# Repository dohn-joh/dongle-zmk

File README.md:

Components for a zmk dongle: a reversible pcb that features mounting holes and wiring for a reset button, and a 3D printed case. The pcb is reversible so that you have the option to mount a reset button to the left or right side of the usb port.

## Files:
- gerbers for a promicro compatible reversible pcb
- 3D models for a case
- ergogen code used to generate the pcb

## Bill of materials:
- 4 M2 screws (5-6mm length)
- 4 M2 heatset inserts (any length <5mm will work)
- Panasonic EVQ-PU[A|C|J|L]02K (side-operated momentary switch)
- microcontroller with promicro footprint
- sockets for the mcu or headers that came with the mcu

## Assembly notes:
- PCB design is intended for the mcu to be mounted face down, such that the RAW pin is in the top left corner. 
- Solder the jumper pads on the same side of the pcb that the mcu is mounted to.

This small project was inspired by https://github.com/spe2/zmk_dongle_hardware.
I used ergogen to generate the pcb and designed the case in fusion360.

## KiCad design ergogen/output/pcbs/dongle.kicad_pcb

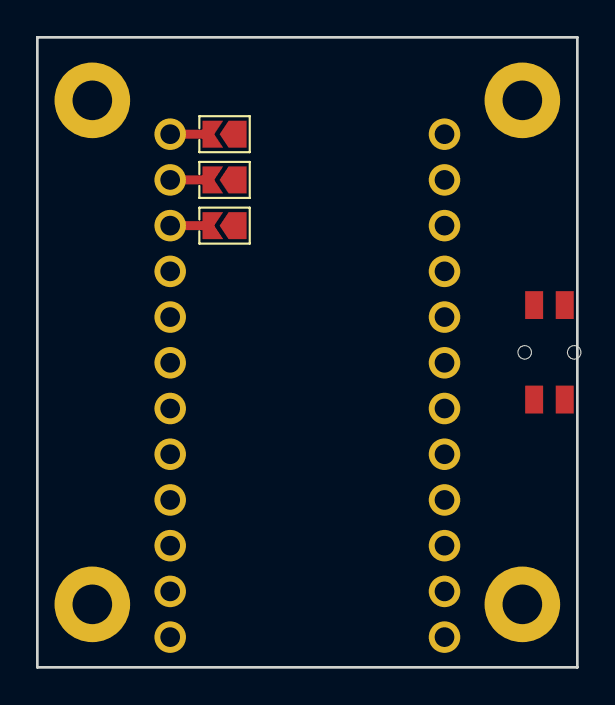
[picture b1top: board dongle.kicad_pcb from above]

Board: 2 copper layers, 30.0 x 35.0 mm, 6 parts (0 on the bottom side), 2 nets, no tracks yet.

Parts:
H1, H2, H3, H4: mounting_hole
MCU1: mcu; promicro
SW1: reset_button; sw_reset_side

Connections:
GND: MCU1.2, SW1.1, SW1.3
RST: MCU1.3, SW1.2, SW1.4

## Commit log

2024-04-02 tested and ready
2024-04-02 added readme
2024-04-02 housekeeping
2024-11-09 update case files
